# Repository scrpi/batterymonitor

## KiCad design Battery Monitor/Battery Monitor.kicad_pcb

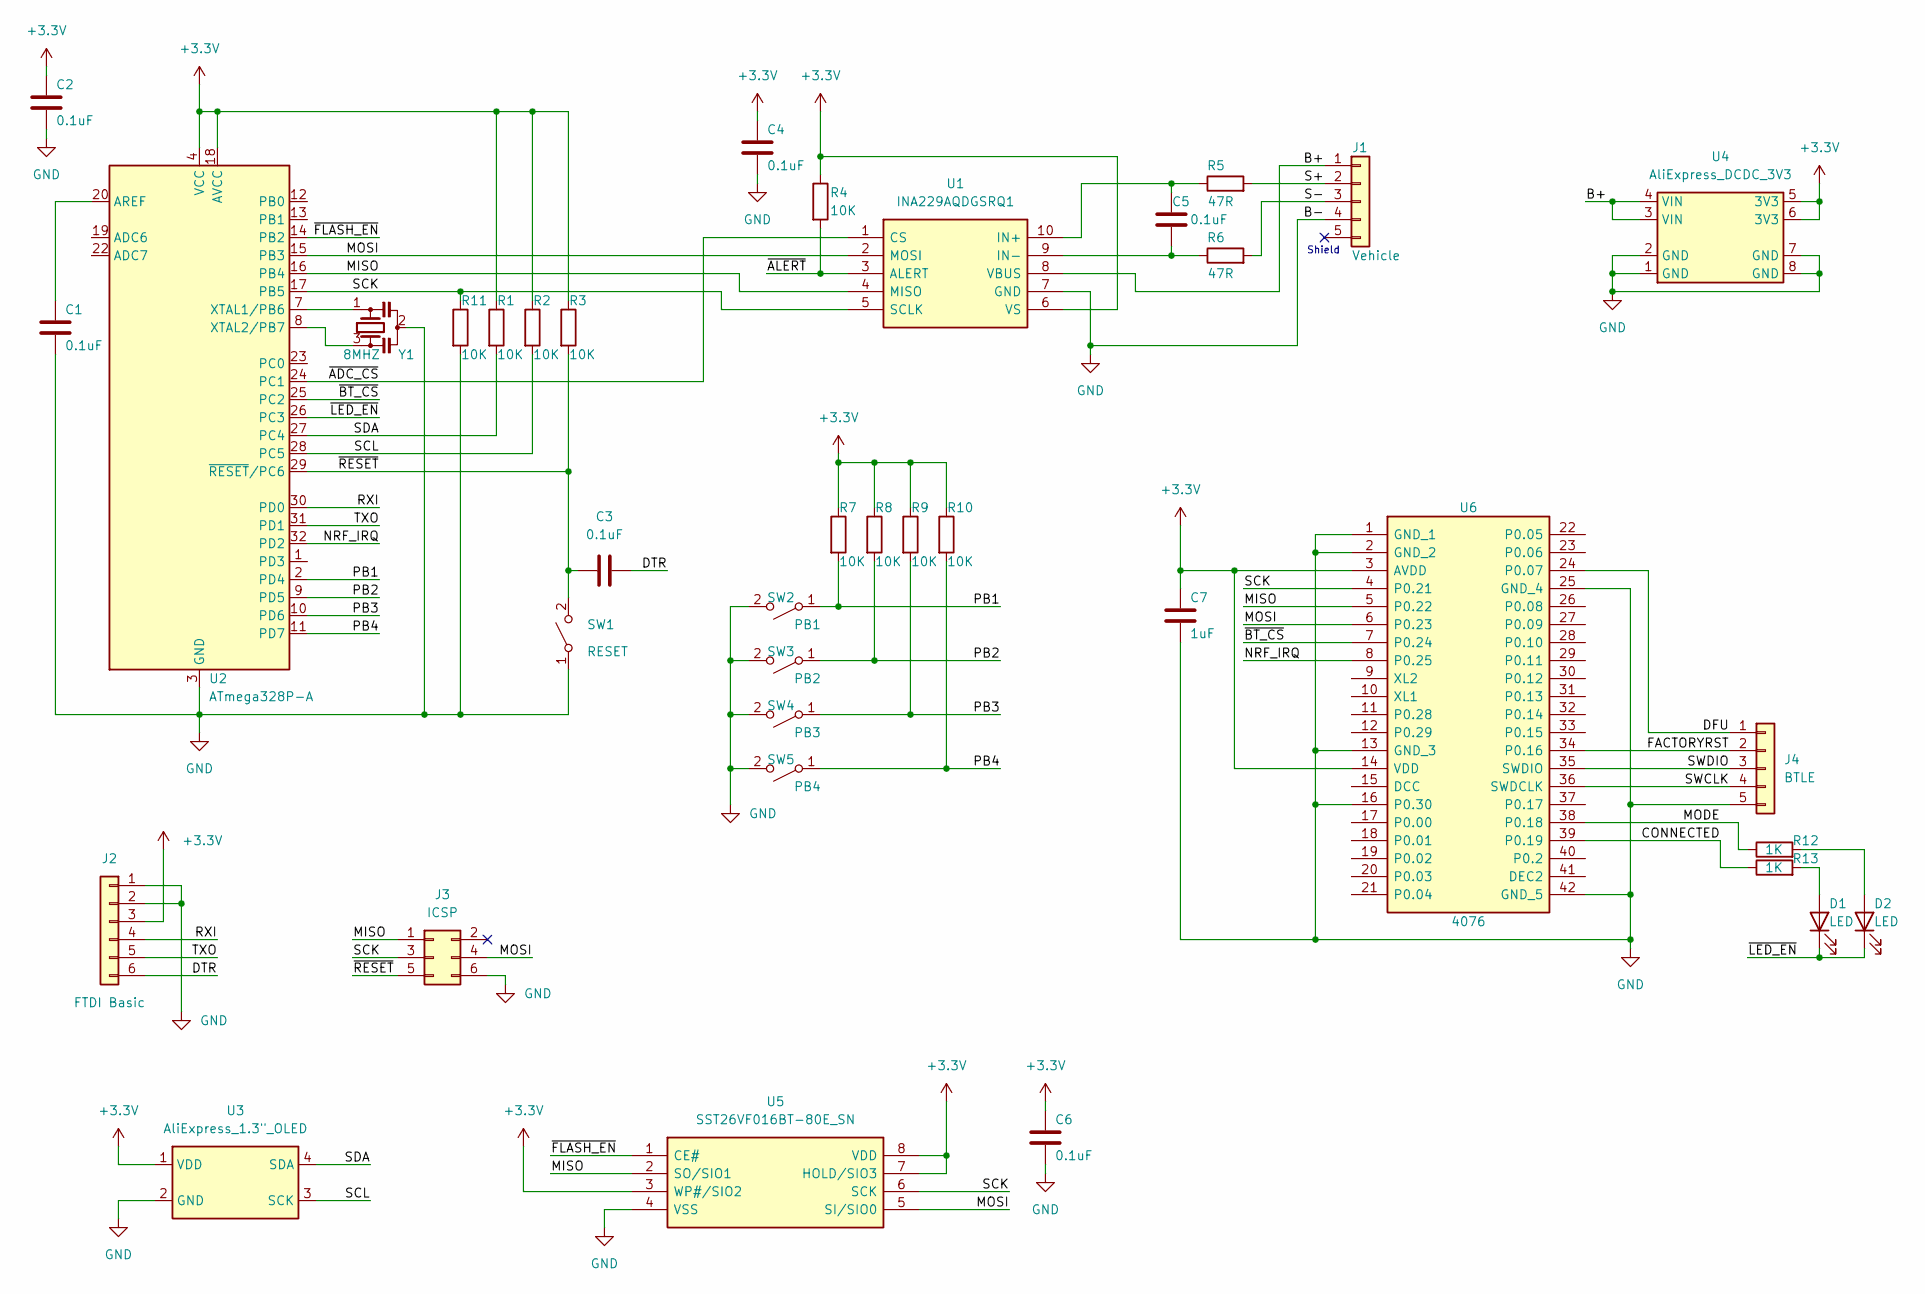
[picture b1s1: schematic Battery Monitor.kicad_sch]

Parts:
C1, C2, C3, C4, C5, C6: 0.1uF; C_0603_1608Metric_Pad1.08x0.95mm_HandSolder
C7: 1uF; C_0603_1608Metric_Pad1.08x0.95mm_HandSolder
D1, D2: LED; LED_0603_1608Metric_Pad1.05x0.95mm_HandSolder
J1: Vehicle; 4400555
J2: FTDI Basic; PinHeader_1x06_P2.54mm_Horizontal
J3: ICSP; PinHeader_2x03_P2.54mm_Vertical
J4: BTLE; PinHeader_1x05_P2.54mm_Vertical
R1, R2, R3, R4, R7, R8, R9, R10, R11: 10K; R_0603_1608Metric_Pad0.98x0.95mm_HandSolder
R5, R6: 47R; R_0603_1608Metric_Pad0.98x0.95mm_HandSolder
R12, R13: 1K; R_0603_1608Metric_Pad0.98x0.95mm_HandSolder
SW1: RESET; PTS526SK15SMTR2LFS
SW2: PB1; TL3301BF160QJ
SW3: PB2; TL3301BF160QJ
SW4: PB3; TL3301BF160QJ
SW5: PB4; TL3301BF160QJ
U1: INA229AQDGSRQ1; SOP50P490X110-10N; Mouser Part Number 595-INA229AQDGSRQ1
U2: ATmega328P-A; TQFP-32_7x7mm_P0.8mm
U3: AliExpress_1.3"_OLED; AliExpress_1.3_OLED
U4: AliExpress_DCDC_3V3; AliExpress_DCDC_SMT
U5: SST26VF016BT-80E_SN; SOIC127P600X175-8N; Mouser Part Number 579-T26VF016BT-80ESN
U6: 4076; Mouser Part Number 485-4076
Y1: 8MHZ; Resonator_SMD_Murata_CSTxExxV-3Pin_3.0x1.1mm_HandSoldering; Part CSTNE8M00G55Z000R0

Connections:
+3V3: C2.1, C4.1, C6.1, C7.1, J2.3, R1.1, R2.1, R3.1, R4.1, R7.1, R8.1, R9.1, R10.1, U1.6 (VS), U2.4 (VCC), U2.6 (VCC), U2.18 (AVCC), U3.1 (VDD), U4.5 (3V3), U4.6 (3V3), U5.3 (WP#/SIO2), U5.7 (HOLD/SIO3), U5.8 (VDD), U6.3 (AVDD), U6.14 (VDD)
/B+: J1.1, U1.8 (VBUS), U4.3 (VIN), U4.4 (VIN)
/CONNECTED: R13.1, U6.39 (P0.19)
/DFU: J4.1, U6.24 (P0.07)
/DTR: C3.2, J2.6
/FACTORYRST: J4.2, U6.34 (P0.16)
/MISO: J3.1, U1.4 (MISO), U2.16 (PB4), U5.2 (SO/SIO1), U6.5 (P0.22)
/MODE: R12.1, U6.38 (P0.18)
/MOSI: J3.4, U1.2 (MOSI), U2.15 (PB3), U5.5 (SI/SIO0), U6.6 (P0.23)
/NRF_IRQ: U2.32 (PD2), U6.8 (P0.25)
/PB1: R7.2, SW2.1 (A), U2.2 (PD4)
/PB2: R8.2, SW3.1 (A), U2.9 (PD5)
/PB3: R9.2, SW4.1 (A), U2.10 (PD6)
/PB4: R10.2, SW5.1 (A), U2.11 (PD7)
/RXI: J2.4, U2.30 (PD0)
/S+: J1.2, R5.2
/S-: J1.3, R6.2
/SCK: J3.3, R11.1, U1.5 (SCLK), U2.17 (PB5), U5.6 (SCK), U6.4 (P0.21)
/SCL: R2.2, U2.28 (PC5), U3.3 (SCK)
/SDA: R1.2, U2.27 (PC4), U3.4 (SDA)
/SWCLK: J4.4, U6.36 (SWDCLK)
/SWDIO: J4.3, U6.35 (SWDIO)
/TXO: J2.5, U2.31 (PD1)
/~ADC_CS: U1.1 (CS), U2.24 (PC1)
/~ALERT: R4.2, U1.3 (ALERT)
/~BT_CS: U2.25 (PC2), U6.7 (P0.24)
/~FLASH_EN: U2.14 (PB2), U5.1 (CE#)
/~LED_EN: D1.1 (K), D2.1 (K), U2.26 (PC3)
/~RESET: C3.1, J3.5, R3.2, SW1.2 (B), U2.29 (~RESET/PC6)
GND: C1.2, C2.2, C4.2, C6.2, C7.2, J1.4, J2.1, J2.2, J3.6, J4.5, R11.2, SW1.1 (A), SW2.2 (B), SW3.2 (B), SW4.2 (B), SW5.2 (B), U1.7 (GND), U2.3 (GND), U2.5 (GND), U2.21 (GND), U3.2 (GND), U4.1 (GND), U4.2 (GND), U4.7 (GND), U4.8 (GND), U5.4 (VSS), U6.1 (GND_1), U6.2 (GND_2), U6.13 (GND_3), U6.16 (P0.30), U6.25 (GND_4), U6.42 (GND_5), Y1.2
unnamed: C1.1, U2.20 (AREF)
unnamed: C5.1, R6.1, U1.9 (IN-)
unnamed: C5.2, R5.1, U1.10 (IN+)
unnamed: D1.2 (A), R13.2
unnamed: D2.2 (A), R12.2
unnamed: U2.7 (XTAL1/PB6), Y1.1
unnamed: U2.8 (XTAL2/PB7), Y1.3

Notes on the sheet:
Shield

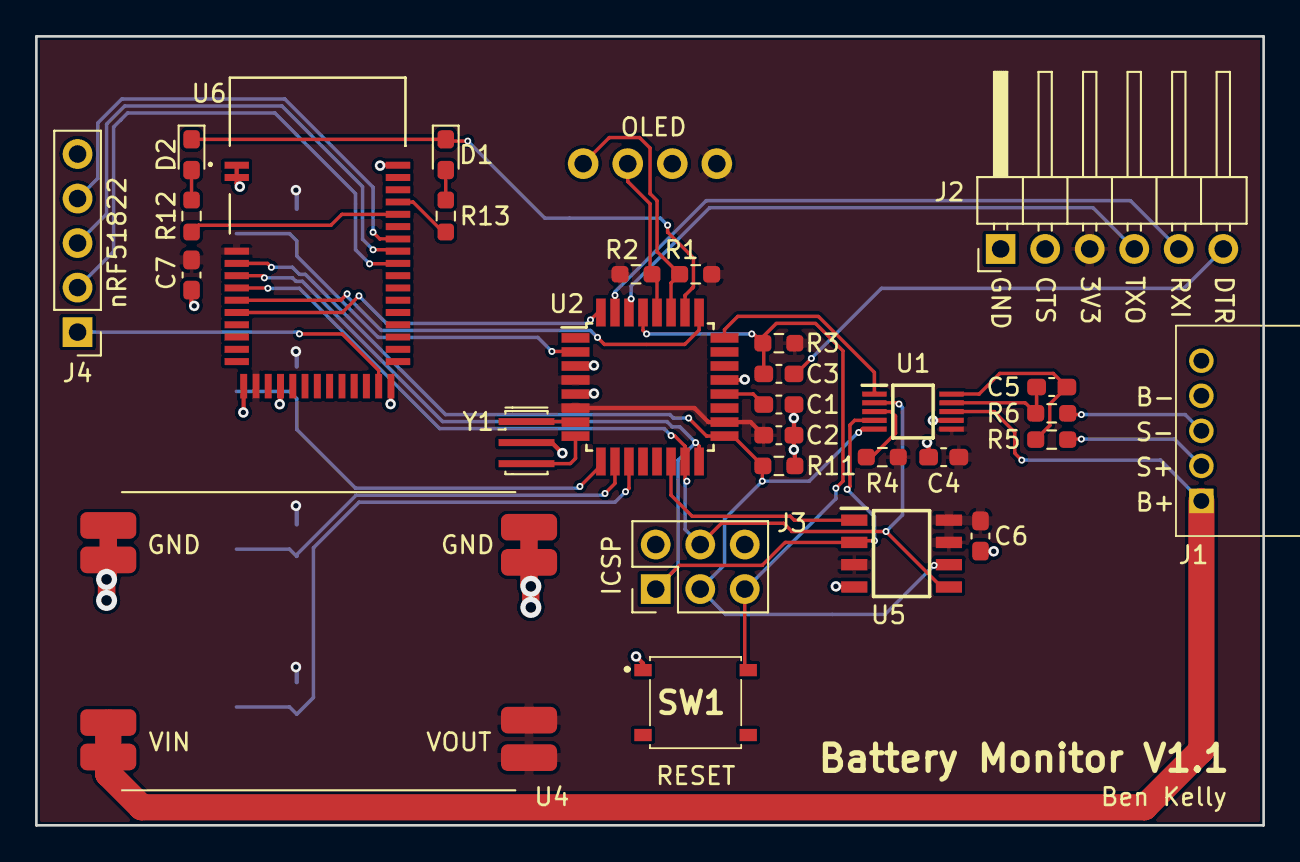
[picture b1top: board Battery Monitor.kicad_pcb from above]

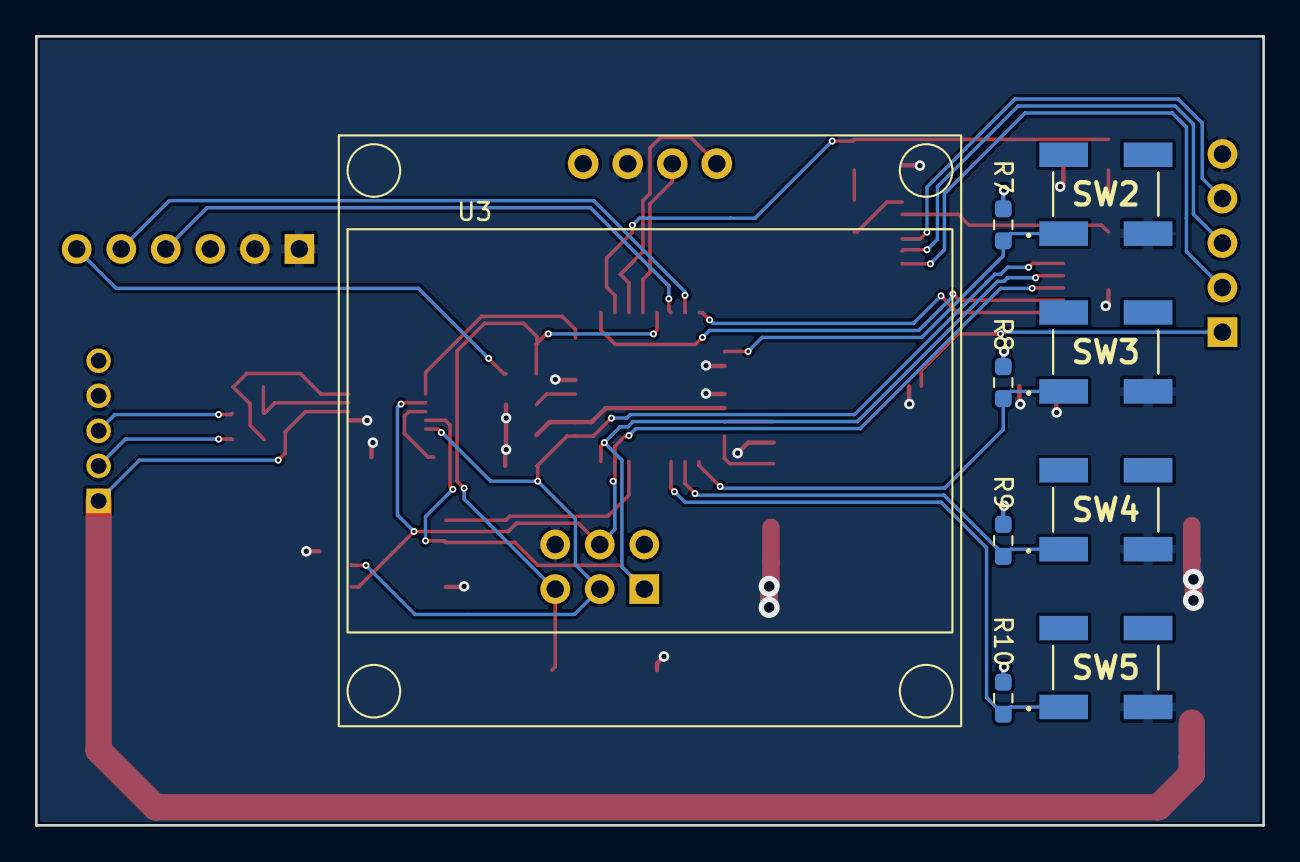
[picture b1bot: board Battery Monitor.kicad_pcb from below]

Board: 2 copper layers, 70.0 x 45.0 mm, 38 parts (9 on the bottom side), 37 nets.

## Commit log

2022-02-09 Initial
    Initial commit
